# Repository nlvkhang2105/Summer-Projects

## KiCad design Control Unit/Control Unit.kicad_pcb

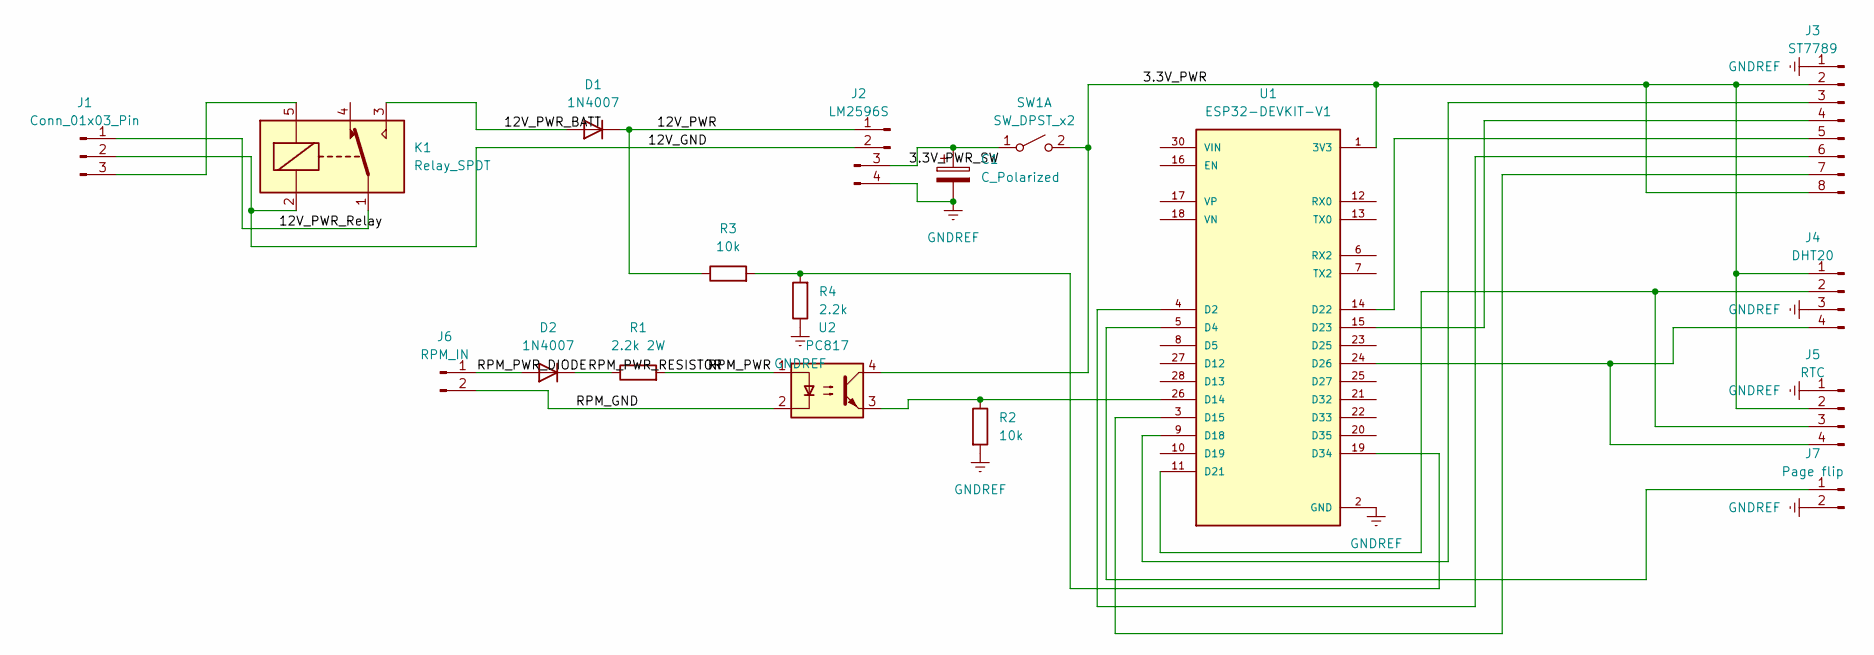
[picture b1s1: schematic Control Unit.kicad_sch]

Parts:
C1: C_Polarized; CP_Radial_D12.5mm_P5.00mm
D1, D2: 1N4007; D_DO-41_SOD81_P10.16mm_Horizontal
J1: Conn_01x03_Pin; SolderWire-1.5sqmm_1x03_P6mm_D1.7mm_OD3mm
J2: LM2596S; LM2596S-footprint-Custom
J3: ST7789; JST_XA_B08B-XASK-1_1x08_P2.50mm_Vertical
J4: DHT20; JST_XA_B04B-XASK-1_1x04_P2.50mm_Vertical
J5: RTC; PinHeader_1x06_P2.54mm_Vertical
J6: RPM_IN; JST_XA_B02B-XASK-1_1x02_P2.50mm_Vertical
J7: Page flip; JST_XA_B02B-XASK-1_1x02_P2.50mm_Vertical
K1: Relay_SPDT; Relay_SPDT_SANYOU_SRD_Series_Form_C
R1: 2.2k 2W; R_Axial_DIN0516_L15.5mm_D5.0mm_P20.32mm_Horizontal
R2, R3: 10k; R_Axial_DIN0207_L6.3mm_D2.5mm_P7.62mm_Horizontal
R4: 2.2k; R_Axial_DIN0207_L6.3mm_D2.5mm_P7.62mm_Horizontal
SW1: SW_DPST_x2; SW_SPDT_CK_JS102011SAQN
U1: ESP32-DEVKIT-V1; MODULE_ESP32_DEVKIT_V1; PARTREV N/A
U2: PC817; DIP-4_W7.62mm

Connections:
/3.3V_PWR: J3.2 (Vcc), J3.8, J4.1 (Vcc), J5.2 (Vcc), SW1.2 (B), U1.1 (3V3), U2.4
/3.3V_PWR_SW: C1.1, J2.3 (3.3V_out), SW1.1 (A)
/12V_GND: J1.2 (GND), J2.2 (12V_GND), K1.2
/12V_PWR: D1.1 (K), J2.1 (12V_in), R3.1
/12V_PWR_BATT: D1.2 (A), K1.3
/12V_PWR_Relay: J1.1 (12V_PWR), K1.1
/RPM_GND: J6.2, U2.2
/RPM_PWR: R1.2, U2.1
/RPM_PWR_DIODE: D2.2 (A), J6.1 (RPM_IN)
/RPM_PWR_RESISTOR: D2.1 (K), R1.1
GNDREF: C1.2, J2.4 (3.3V_GND), J3.1 (GND), J4.3 (GND), J5.1 (GND), J7.2, R2.2, R4.1, U1.2 (GND), U1.29 (GND)
unnamed: J1.3 (12V_SWITCH), K1.5
unnamed: J3.7 (CS), U1.3 (D15)
unnamed: J3.6 (DC), U1.4 (D2)
unnamed: J3.5 (RES), U1.14 (D22)
unnamed: J3.3 (SCL), U1.9 (D18)
unnamed: J3.4 (SDA), U1.15 (D23)
unnamed: J4.4 (SCL), J5.4 (SCL), U1.24 (D26)
unnamed: J4.2 (SDA), J5.3 (SDA), U1.11 (D21)
unnamed: J7.1 (SIG), U1.5 (D4)
unnamed: R2.1, U1.26 (D14), U2.3
unnamed: R3.2, R4.2, U1.19 (D34)

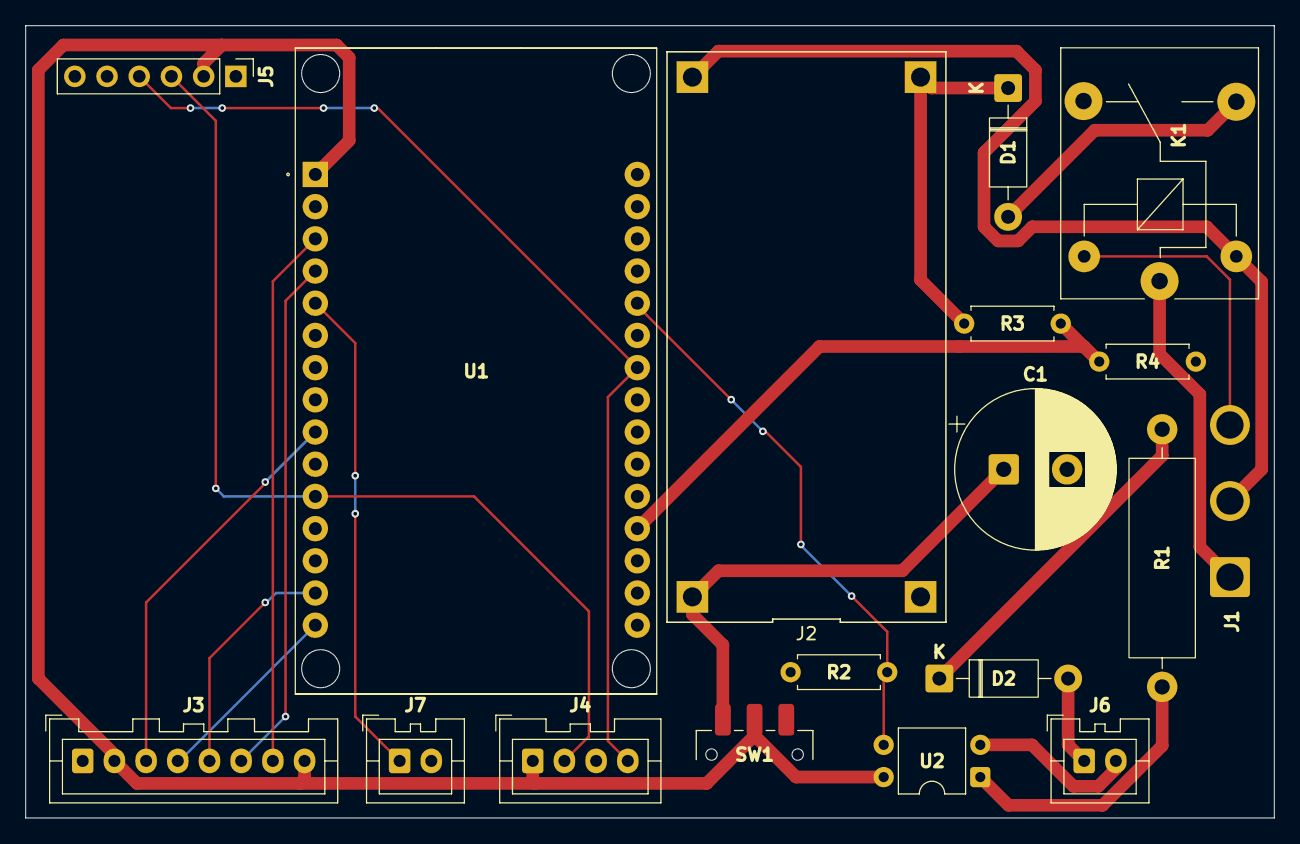
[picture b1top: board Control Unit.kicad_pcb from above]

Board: 2 copper layers, 98.5 x 62.5 mm, 18 parts (0 on the bottom side), 22 nets.

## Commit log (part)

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2026-06-26 beta 1.0
2026-06-27 rev 1.0
2026-06-29 rev 1.1: added relay to use power directly from battery
2026-06-29 rev 1.1b: optimized PCB size
